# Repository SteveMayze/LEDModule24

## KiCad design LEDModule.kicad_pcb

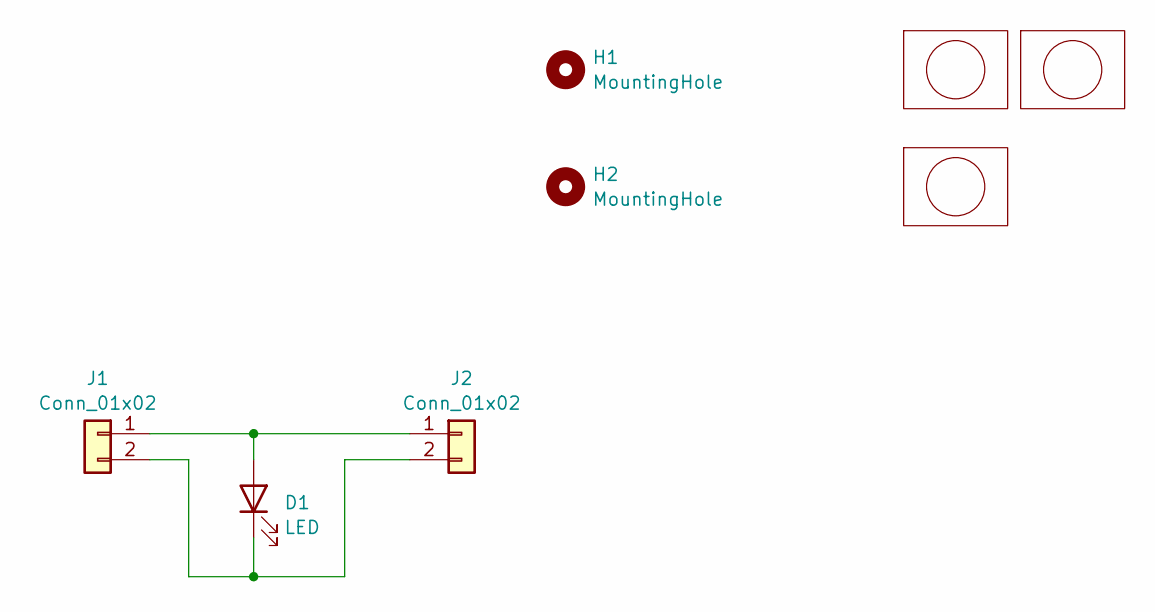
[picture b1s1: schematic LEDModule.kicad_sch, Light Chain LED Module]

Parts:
D1: LED; LED_D10.0mm; MPN 10003R1C-CSA-A
H1, H2: MountingHole; MountingHole_2.7mm_M2.5
J1, J2: Conn_01x02; Molex_SPOX_5268-02A_1x02_P2.50mm_Horizontal; MPN 5268-02A / 2205-7025
Lg1, Lg3: logo; MyBasic_rounded_50_1
Lg2: logo; KiCad-Logo2_5mm_SilkScreen

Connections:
unnamed: D1.2 (A), J1.1, J2.1
unnamed: D1.1 (K), J1.2, J2.2

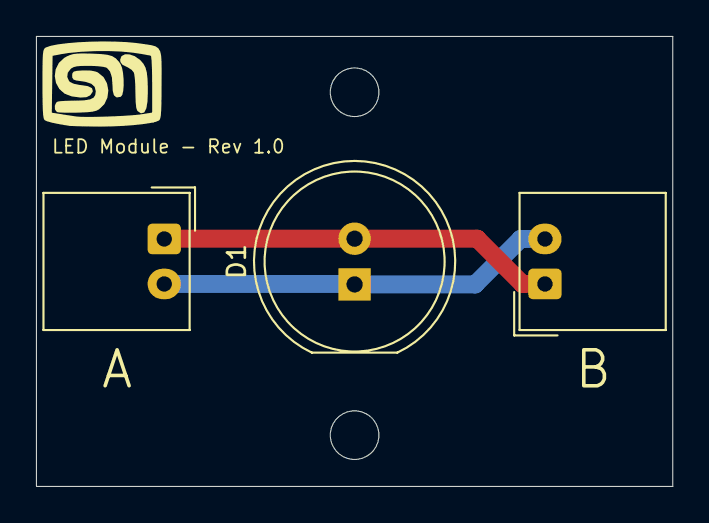
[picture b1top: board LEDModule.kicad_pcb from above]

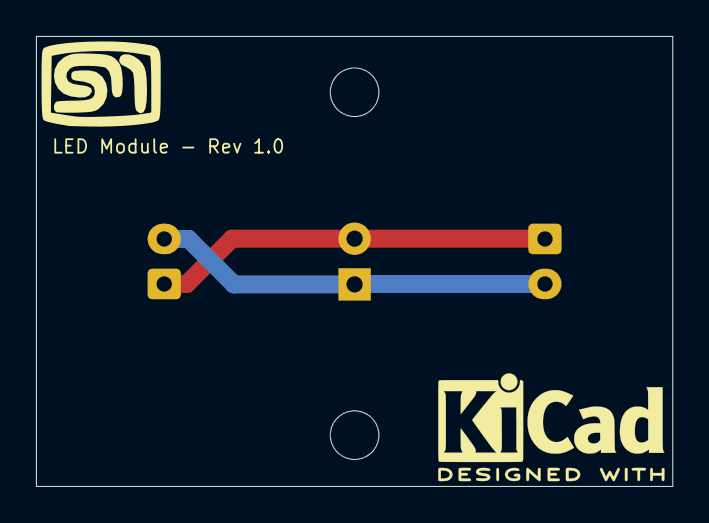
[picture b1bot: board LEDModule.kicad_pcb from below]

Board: 2 copper layers, 35.3 x 25.0 mm, 8 parts (2 on the bottom side), 2 nets.

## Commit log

2024-09-15 Initial checking
2024-09-15 Molex 3D model for OS
